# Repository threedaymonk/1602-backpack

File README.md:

# 1602 Backpack

A small backpack board to add any or all of the following to a 1602 LCD display
(and other variants with similar pinouts, like 2004):

- contrast adjustment trimmer
- supply backlight from VDD/VSS
- set to write-only mode
- simplify the connection to 8 pins

There are three connector footprints. The topmost is for attaching to the back
of the display module. The middle footprint exposes the same 16 pins. The
lower footprint has eight pins: VSS, VDD (5V), RS, E, and four data lines D4-D7.

## Contrast adjustment

Install a 10K trimmer potentiometer. If you're using the long connector (in the
middle) don't solder a pin at pin 3 (VO)

## Backlight

Solder the two jumpers labelled "Backlight". Do not use pins 15 and 16 of the
long connector.

## Write-only

Does anyone ever read from these displays? If you're interfacing from a 3.3V
device, you won't want to. This jumper is essential when using the shorter
connector.

## How to ...

### Connect to an Arduino or Raspberry Pi with 8 wires

- Solder all three jumpers (Backlight and Write only)
- Solder a header to the short 8-pin connector
- Install a 10K trimmer

If using a 3.3V device, note that VDD still has to be 5V.

### Add contrast adjustment to a device without it (e.g. Kawai K1r)

- Install a 10K trimmer
- Remove pin 3 (VO) from a 1x16 header and solder it to the long
  connector footprint.

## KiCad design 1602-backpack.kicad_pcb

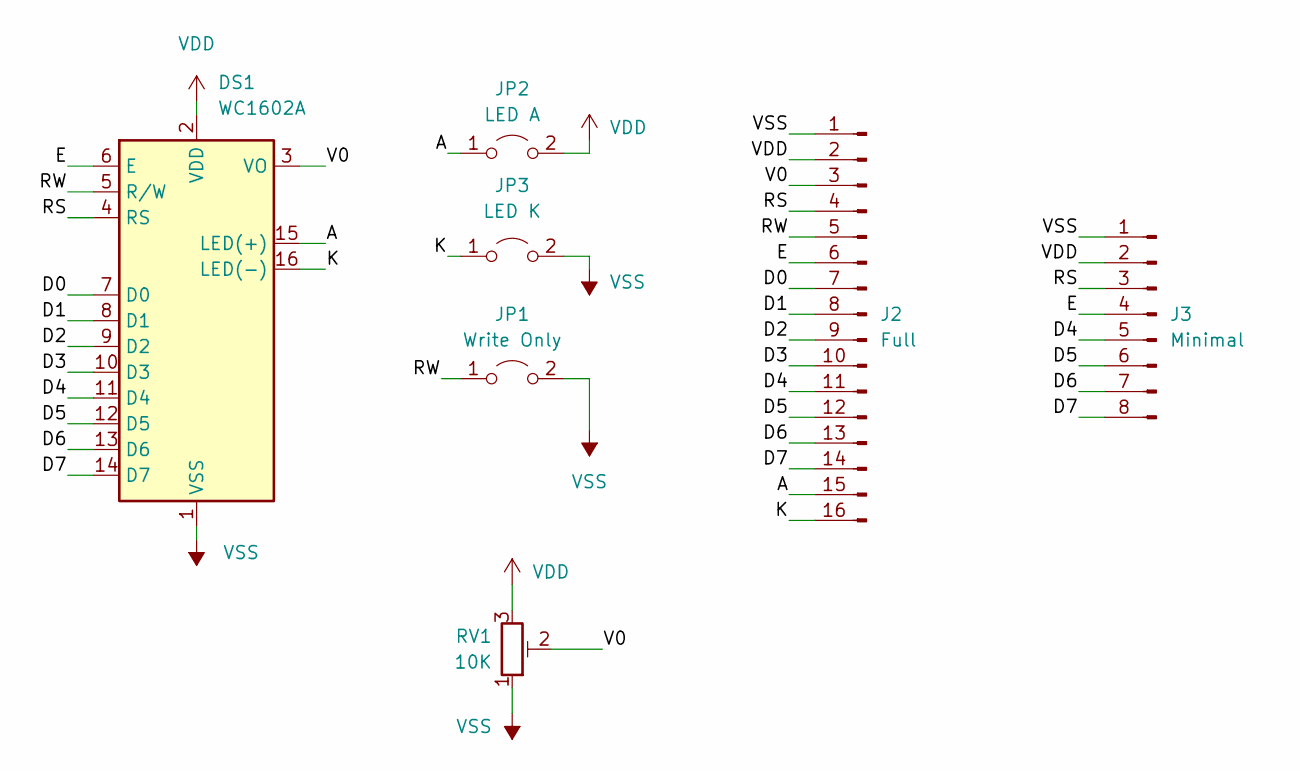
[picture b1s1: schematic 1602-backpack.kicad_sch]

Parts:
DS1: WC1602A; PinSocket_1x16_P2.54mm_Vertical
J2: Full; PinHeader_1x16_P2.54mm_Vertical
J3: Minimal; PinHeader_1x08_P2.54mm_Vertical
JP1: Write Only; SolderJumper
JP2: LED A; SolderJumper
JP3: LED K; SolderJumper
RV1: 10K; Potentiometer_6mm_Trimmer

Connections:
/A: DS1.15 (LED(+)), J2.15, JP2.1 (A)
/D0: DS1.7 (D0), J2.7
/D1: DS1.8 (D1), J2.8
/D2: DS1.9 (D2), J2.9
/D3: DS1.10 (D3), J2.10
/D4: DS1.11 (D4), J2.11, J3.5
/D5: DS1.12 (D5), J2.12, J3.6
/D6: DS1.13 (D6), J2.13, J3.7
/D7: DS1.14 (D7), J2.14, J3.8
/E: DS1.6 (E), J2.6, J3.4
/K: DS1.16 (LED(-)), J2.16, JP3.1 (A)
/RS: DS1.4 (RS), J2.4, J3.3
/RW: DS1.5 (R/W), J2.5, JP1.1 (A)
/V0: DS1.3 (VO), J2.3, RV1.2
VDD: DS1.2 (VDD), J2.2, J3.2, JP2.2 (B), RV1.3
VSS: DS1.1 (VSS), J2.1, J3.1, JP1.2 (B), JP3.2 (B), RV1.1

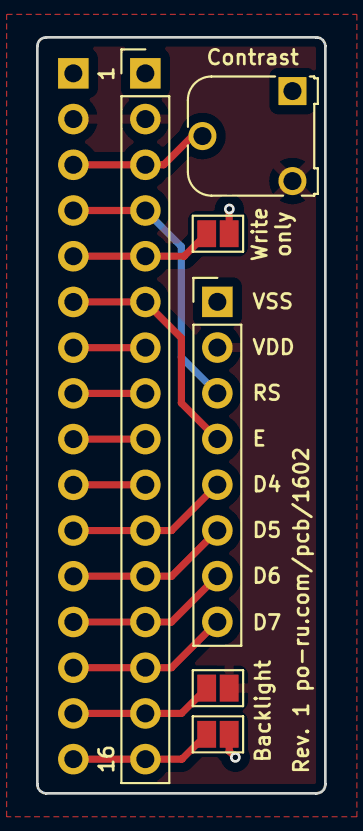
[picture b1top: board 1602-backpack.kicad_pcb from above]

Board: 2 copper layers, 16.0 x 42.0 mm, 7 parts (1 on the bottom side), 16 nets.

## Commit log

2022-10-03 Initial empty commit
2022-10-03 Initial PCB
2022-10-30 Ignore JLC-specific files
2022-10-30 Add LICENSE
2022-10-30 Add README
2022-10-30 Finalise layout and round corners
2022-10-30 Correct board
    Specify order number location, remove unused copper layers, tweak size
    and legend.
2022-10-30 Add photo
2022-10-30 Improve README
